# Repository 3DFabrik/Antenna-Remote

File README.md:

# Antenna Remote

Ein Antennenumschalter für bis zu acht Antennen auf einem ESP32. Er wählt die Antenne nach der Frequenz des Transceivers (Automatik) oder von Hand, zeigt alles auf einem Touch-Display und lässt sich über WLAN, Bluetooth und eine Weboberfläche bedienen. [SDROxide](https://github.com/3DFabrik/sdroxide) kann ihm die Frequenz direkt über WLAN schicken. Die Firmware ist eine Weiterentwicklung der Antenna Remote II.

Gedacht ist die Einheit für die Fernumschalter von [Amplitec](https://www.amplitec.hu/r_sw_3000_4_way_eng.html) (SW:3000) mit vier, sechs oder acht Wegen. Sie schaltet positiv und passt damit zu Umschaltern mit gemeinsamer Masse. Die Anzahl der Antennen (bis zu acht) wird in den Einstellungen gewählt.

Die Firmware-Version steht oben in der Weboberfläche. Ein Release-Build trägt den Tag als Version, ein lokaler Build seine Bauzeit.

## Was dazugehört

- **ESP32** Dev Module, 4 MB Flash. Die Partition `min_spiffs` hält zwei Programme vor, damit ein Update über WLAN möglich ist.
- **Touch-Display** ST7789, 320 × 240, quer eingebaut, mit Touch-Controller.
- **Schieberegister** 74HC164 für die Relais der acht Antennen. Genau ein Ausgang ist aktiv.
- **ICOM-Anschluss** (optional): CI-V an `Serial2` (19200 Baud, GPIO 16 und 17). Der Umschalter liest damit die Frequenz eines Icom. Andere Funkgeräte meldet ein `rigctld` im WLAN, siehe *Frequenzquelle*.

| Funktion | GPIO |
| --- | --- |
| Display MOSI, SCLK, MISO | 4, 18, 19 |
| Display CS, DC, RST | 15, 2, 23 |
| Touch CS | 21 |
| Schieberegister CLR, A/B, CLK | 25, 26, 27 |
| Relais externer Tuner, Relais Tune-Anforderung | 33, 32 |

Die Display-Pins stehen in `libraries/TFT_eSPI/User_Setup.h`. Beim ersten Start fragt das Display nach der Touch-Kalibrierung.

## Bedienung am Gerät

- **Seite 1** zeigt Frequenz, Band und die Antennenliste. `AUTOMATIC MODE` schaltet zwischen Automatik und Handbetrieb um. Zwischen diesem Schalter und `MISC` stehen zwei Symbole für die Verbindung: im Bluetooth-Modus das Bluetooth-Zeichen (grün, solange ein Client verbunden ist), im WLAN-Modus die Signalstärke (drei Bögen) und ein Bildschirm-Symbol, das grün wird, solange SDROxide verbunden ist. Die Weboberfläche zeigt dasselbe oben rechts. Im Handbetrieb wählen UP und DN die Antenne. Hält man `ST` eine Sekunde, wird die aktuelle Antenne für das aktuelle Band gespeichert. Im Automatikmodus heißt dieselbe Taste `TU` und startet den Tuner, siehe unten.
- **Seite 2** (`MISC`) zeigt die Verbindung: Modus, SSID, Status, IP, Signal, ob SDROxide verbunden ist, Antenne und Automatik. Hier wird auch der Verbindungsmodus eingestellt.

## Tuner

In den Einstellungen der Weboberfläche lässt sich pro Antenne das Häkchen `External Tuner` setzen. Ist es für die gewählte Antenne gesetzt, schaltet der Umschalter das erste Relais (GPIO 33) für den externen Tuner. Damit ist der Antennentuner des Transceivers abgeschaltet.

Die Taste `TU` (Display, Automatikmodus) und `TUNING` (Weboberfläche) sind nur dann aktiv, wenn die gewählte Antenne diese Markierung hat. Sonst sind sie grau. Ein Druck löst über das zweite Relais (GPIO 32) für genau fünf Sekunden die Tune-Anforderung aus, auch wenn der Finger auf der Taste bleibt. Der Transceiver sendet dann ein Signal mit geringer Leistung, auf das sich der externe Tuner abstimmt. Während der Anforderung ist die Taste rot. Ein erneuter Druck bricht sie ab, ebenso ein Wechsel der Antenne oder des Modus.

## Frequenzquelle und Bänder

In den Einstellungen der Weboberfläche wählt man unter *Frequency source*, woher der Umschalter die Frequenz liest:

- **None:** Er liest keine Frequenz. Sie kann trotzdem vom Windows-Programm mit `<QRG,…>` (USB oder Bluetooth) kommen.
- **Icom CI-V:** Er liest die Frequenz eines Icom über `Serial2`. Der TRX-Typ wird dazu gewählt. Einmal pro Sekunde fragt er auch den Sendezustand ab (CI-V-Befehl `1C 00`). Antwortet das Funkgerät darauf nicht, gibt es keine RX/TX-Anzeige.
- **Hamlib rigctld:** Im WLAN-Modus verbindet er sich mit einem `rigctld` (Hamlib), flrig oder dem Hamlib-Server von SDROxide und fragt zweimal pro Sekunde die Frequenz (`f`) und den Sendezustand (`t`) ab. Host (am besten als IP-Adresse) und Port (Vorgabe 4532) werden eingetragen. Ein Beispiel für Hamlib: `rigctld -m <Modell> -r COM3 -s 19200 -T 0.0.0.0`, die Modellnummer zeigt `rigctld -l`. `rigctld` hat keine Anmeldung und muss im LAN erreichbar sein, deshalb nur im Heimnetz einsetzen. Der Umschalter schickt nur Lesebefehle.
- **SDROxide:** SDROxide verbindet sich mit dem Umschalter (Port 4540) und schickt die Frequenz, siehe unten. Die Frequenz von SDROxide wird nur bei dieser Auswahl übernommen. Die übrigen Befehle (Antenne wählen, Automatik) funktionieren bei jeder Quelle. Den Sendezustand meldet SDROxide mit dem Befehl `P`, siehe Tabelle unten.

Oben rechts in der Weboberfläche steht neben der WLAN-Stärke die gewählte Quelle (`CI-V`, `Hamlib` oder `SDROxide`). Der Punkt davor leuchtet grün, solange die Verbindung steht. Das Display zeigt neben dem Band `RX` (grün) oder `TX` (rot), sobald die Quelle den Sendezustand liefert. Die Weboberfläche zeigt dasselbe oben links in der LCD-Anzeige. Beim Senden kommt dort das SWR dazu: bei `rigctld` per `l SWR`, sofern das Funkgerät es meldet (SDROxides eigener Hamlib-Server tut das nicht), bei Icom CI-V per `15 12` (nach der SWR-Skala des Icom, über 3 nur grob) und bei SDROxide mit dem Befehl `W`.

Auf Seite 2 steht die Quelle in der Zeile `SOURCE`. Auch über die serielle Konsole lässt sie sich setzen: `<freq_src,0>` (keine), `<freq_src,1>` (CI-V), `<freq_src,2>` (rigctld) oder `<freq_src,3>` (SDROxide), dazu `<rig_host,192.168.1.20>` und `<rig_port,4532>`.

**Sendeschutz:** Meldet die Quelle, dass das Funkgerät sendet, schaltet der Umschalter keine Antenne um. Der Wechsel (Automatik, Handbetrieb oder Weboberfläche) wird erst am Ende des Sendens ausgeführt, bis dahin steht `waiting for RX` auf der Webseite. Bricht die Meldung ab, gilt das als Empfang. Der Sendezustand kommt bei `rigctld` vom Befehl `t`, bei CI-V von `1C 00` und bei SDROxide vom Befehl `P`. Meldet eine Quelle ihn nicht, steht das in den Einstellungen und es gibt weder RX/TX-Anzeige noch Schutz.

**Bandgrenzen:** In den Einstellungen unter *Band limits* stehen Unter- und Obergrenze jedes Bandes in kHz. Die Vorgabe ist Region 1. Mit der Auswahl gibt es Voreinstellungen für Region 2 und 3, jeder Wert lässt sich verändern. Steht bei einem Band 0 und 0, ist es abgeschaltet. Liegt die Frequenz in keinem Band, bleibt die Antenne wie sie ist.

## Verbindung: Bluetooth oder WLAN

Der Umschalter läuft entweder mit Bluetooth oder mit WLAN, nie mit beidem. Auf Seite 2 wechselt `BT -> WLAN` (bzw. `WLAN -> BT`) den Modus. Das Gerät startet danach neu, und der Wechsel muss einmal bestätigt werden.

**WLAN einrichten:** Im WLAN-Modus öffnet `WLAN setup` eine Netzliste mit Scan. Das Netz antippen und das Passwort mit der Bildschirmtastatur eingeben (`Show` zeigt es im Klartext). Versteckte Netze gibt es über `HIDDEN`. Der Status auf Seite 2 nennt Fehler im Klartext, zum Beispiel `SSID not found` oder `Wrong password?`. Das Passwort liegt getrennt von der Konfiguration im Flash und wird nie ausgegeben.

Über die serielle Konsole (115200 Baud) geht es auch:

| Befehl | Wirkung |
| --- | --- |
| `<WIFI,ssid,passwort>` | speichert das WLAN (das Passwort darf Kommas enthalten) |
| `<NETMODE,wifi>` oder `<NETMODE,bt>` | Modus wählen, danach Neustart |
| `<WIFISTATUS>` | Modus, SSID, Status, IP und Signal |

## Weboberfläche

Im WLAN-Modus ist der Umschalter unter `http://<IP-Adresse>/` erreichbar. Die Seite passt sich der Fenstergröße an.

- **Main:** Frequenz in einer LCD-Anzeige, eine Taste pro Antenne, `AUTOMATIC`, `INT TUNER` und `TUNING`.
- **Settings:** Antennenanzahl, Namen, externer Tuner pro Antenne, Zuordnung der Bänder 160 bis 4 m, Bandgrenzen und Frequenzquelle. `Reboot` startet neu. `Reset` stellt die Werkseinstellungen her, behält aber den WLAN-Modus.
- **Update:** Firmware über den Browser einspielen, siehe unten.

Es gibt kein Passwort, der Umschalter gehört ins Heimnetz. Änderungen nimmt er nur per POST mit einem eigenen Header an, damit eine fremde Webseite ihn nicht schalten kann.

## SDROxide

In SDROxide unter Settings → Radio den Haken `Use Antenna Remote` setzen und unter Settings → Servers die IP-Adresse des Umschalters eintragen. Im Umschalter unter *Frequency source* `SDROxide` wählen. SDROxide zeigt dort, ob die Verbindung steht, und schickt die Frequenz des Radios. Die Automatik des Umschalters wählt danach die Antenne.

Das Protokoll ist Text über TCP, Port 4540, eine Zeile pro Befehl. Es kommt immer nur ein Client zum Zug. Ein weiterer wird abgewiesen, solange der erste mindestens einmal in zwei Sekunden fragt. Schweigt er länger, übernimmt ein neuer Client die Verbindung, nach fünf Sekunden Stille wird er getrennt.

| Anfrage | Antwort |
| --- | --- |
| `v` | `AntennaRemote 1` und `RPRT 0` |
| `F <Hz>` | `RPRT 0` (Frequenz des Radios in Hertz) |
| `s` | `ant=<1-8> auto=<0\|1> band=<m> n=<Anzahl> name=<Text>` und `RPRT 0` |
| `M <0\|1>` | `RPRT 0` (Automatik aus oder ein, ab Version 1.1.0) |
| `P <0\|1>` | `RPRT 0` (das Funkgerät empfängt oder sendet, ab Version 1.4.0; sollte bei jeder Änderung und mindestens alle 5 Sekunden kommen) |
| `W <SWR>` | `RPRT 0` (das SWR beim Senden, zum Beispiel `W 1.5`, ab Version 1.4.0; etwa zweimal pro Sekunde, solange gesendet wird) |
| `A <n>` | `RPRT 0` (Antenne `n` wählen und auf Handbetrieb schalten, ab Version 1.2.0) |

Alles andere beantwortet der Umschalter mit `RPRT -1`. SDROxide zeigt die aktive Antenne, einen Schalter für die Automatik und im Handbetrieb Tasten zum Weiterschalten in der Kopfleiste (Box `ANT SW`).

## Windows-Programm

Das Windows-Programm Antenna Remote V2 läuft weiter über Bluetooth oder die serielle Schnittstelle, auch mit OmniRig. Die Befehle in der Form `<ANTNUMBER,3,0>` sind unverändert. Antennen und Bandzuordnung lassen sich jetzt aber auch in der Weboberfläche pflegen.

## Firmware einspielen

Die Release-Dateien stehen unter *Releases*:

- `Antenna-Remote_ota.bin` ist das Programm für das **Update im Browser** (Reiter *Update*) oder per `curl`:
  `curl -H "X-AR: 1" -F "firmware=@Antenna-Remote_ota.bin" http://<IP>/update`
  Das Update läuft nur im WLAN-Modus. Vorher sollte nicht gesendet werden, denn der Umschalter startet danach neu.
  Die Weboberfläche prüft über den Browser (höchstens einmal am Tag) auf GitHub, ob es eine neuere Version gibt, und zeigt dann oben einen Hinweis mit Link zum Reiter *Update*. Dort führt ein Link zu den Dateien des Releases.
- `Antenna-Remote.bin` ist das Abbild für **USB**. Es wird ab Adresse 0 geschrieben:
  `esptool.py --chip esp32 write_flash 0x0 Antenna-Remote.bin`

## Selbst bauen

Arduino IDE oder `arduino-cli` mit dem Board-Paket `esp32:esp32` in Version **2.0.17**. Die mitgelieferte TFT_eSPI passt zu dieser Version, die Core-Reihe 3 baut sie nicht.

```
arduino-cli compile --fqbn esp32:esp32:esp32:PartitionScheme=min_spiffs --libraries libraries .
```

Die Bibliothek `libraries/TFT_eSPI` enthält die Pinbelegung des Displays. Beim Bauen in der Arduino IDE den Ordner `libraries` als Sketchbook-Bibliothek eintragen oder die Bibliothek dorthin kopieren.

## Release über GitHub

Ein Tag `v…` baut die Firmware auf GitHub und legt ein Release mit beiden Dateien an:

```
git tag v1.0.0
git push origin v1.0.0
```

Alternativ startet man *Actions → Release → Run workflow* und gibt die Version ein. Der Ablauf steht in `.github/workflows/release.yml`.

## Hardware

Die Platine liegt unter `hardware/` (KiCad):

- `kicad/` Projekt (Schaltplan, Leiterplatte), Stückliste und Netzliste
- `production/` Gerber- und Bohrdateien, `BOM.xlsx`
- `docs/` Schaltplan als PDF, Anschlussplan des Amplitec-Kabels
- `parts/` ESP32-DevKitC (Symbol, Footprint, 3D-Modell)
- `3d/` STEP-Modell der Platine

**Anschluss des Antennenumschalters (J1, DB9-Buchse):** Die Platine schaltet positiv. Die Relais des Amplitec-Umschalters hängen mit ihrem gemeinsamen Minus an Masse (Pin 3). Die Belegung folgt dem Plan von Amplitec (`hardware/docs/RSW(4)(6)8A1R_DSUB9_Connectors.pdf`). Antenne *n* schaltet das Relais `RLYn`:

| DB9-Pin | 1 | 2 | 3 | 4 | 5 | 6 | 7 | 8 | 9 |
| --- | --- | --- | --- | --- | --- | --- | --- | --- | --- |
| Signal | RLY8 | RLY7 | GND | RLY6 | RLY5 | RLY4 | RLY3 | RLY2 | RLY1 |

Beim 8-fach-Umschalter sind alle Pins belegt. Der 6-fach braucht Pin 3 und 4 bis 9, der 4-fach Pin 3 und 6 bis 9. Das Kabel hat an beiden Enden einen 9-poligen Stecker (male), der Schirm liegt am Metallgehäuse. Amplitec empfiehlt 0,25 mm² bis 70 m und 0,5 mm² bis 100 m Länge sowie einen Test des fertigen Kabels.

**Bekannte Fehler:**

- Der Buzzer (BZ1) ist im Schaltplan nicht richtig angeschlossen. Er hängt an GPIO 34, und der kann nur Eingang. Der Pin muss getauscht werden. Die Firmware steuert noch keinen Buzzer an.
- Der Buzzer sitzt auf der Leiterplatte zu nah am Rand und muss etwas weiter nach innen.

## Lizenz

MIT, siehe `LICENSE`. Die Bibliothek TFT_eSPI unter `libraries/TFT_eSPI` hat ihre eigene Lizenz (`license.txt`).

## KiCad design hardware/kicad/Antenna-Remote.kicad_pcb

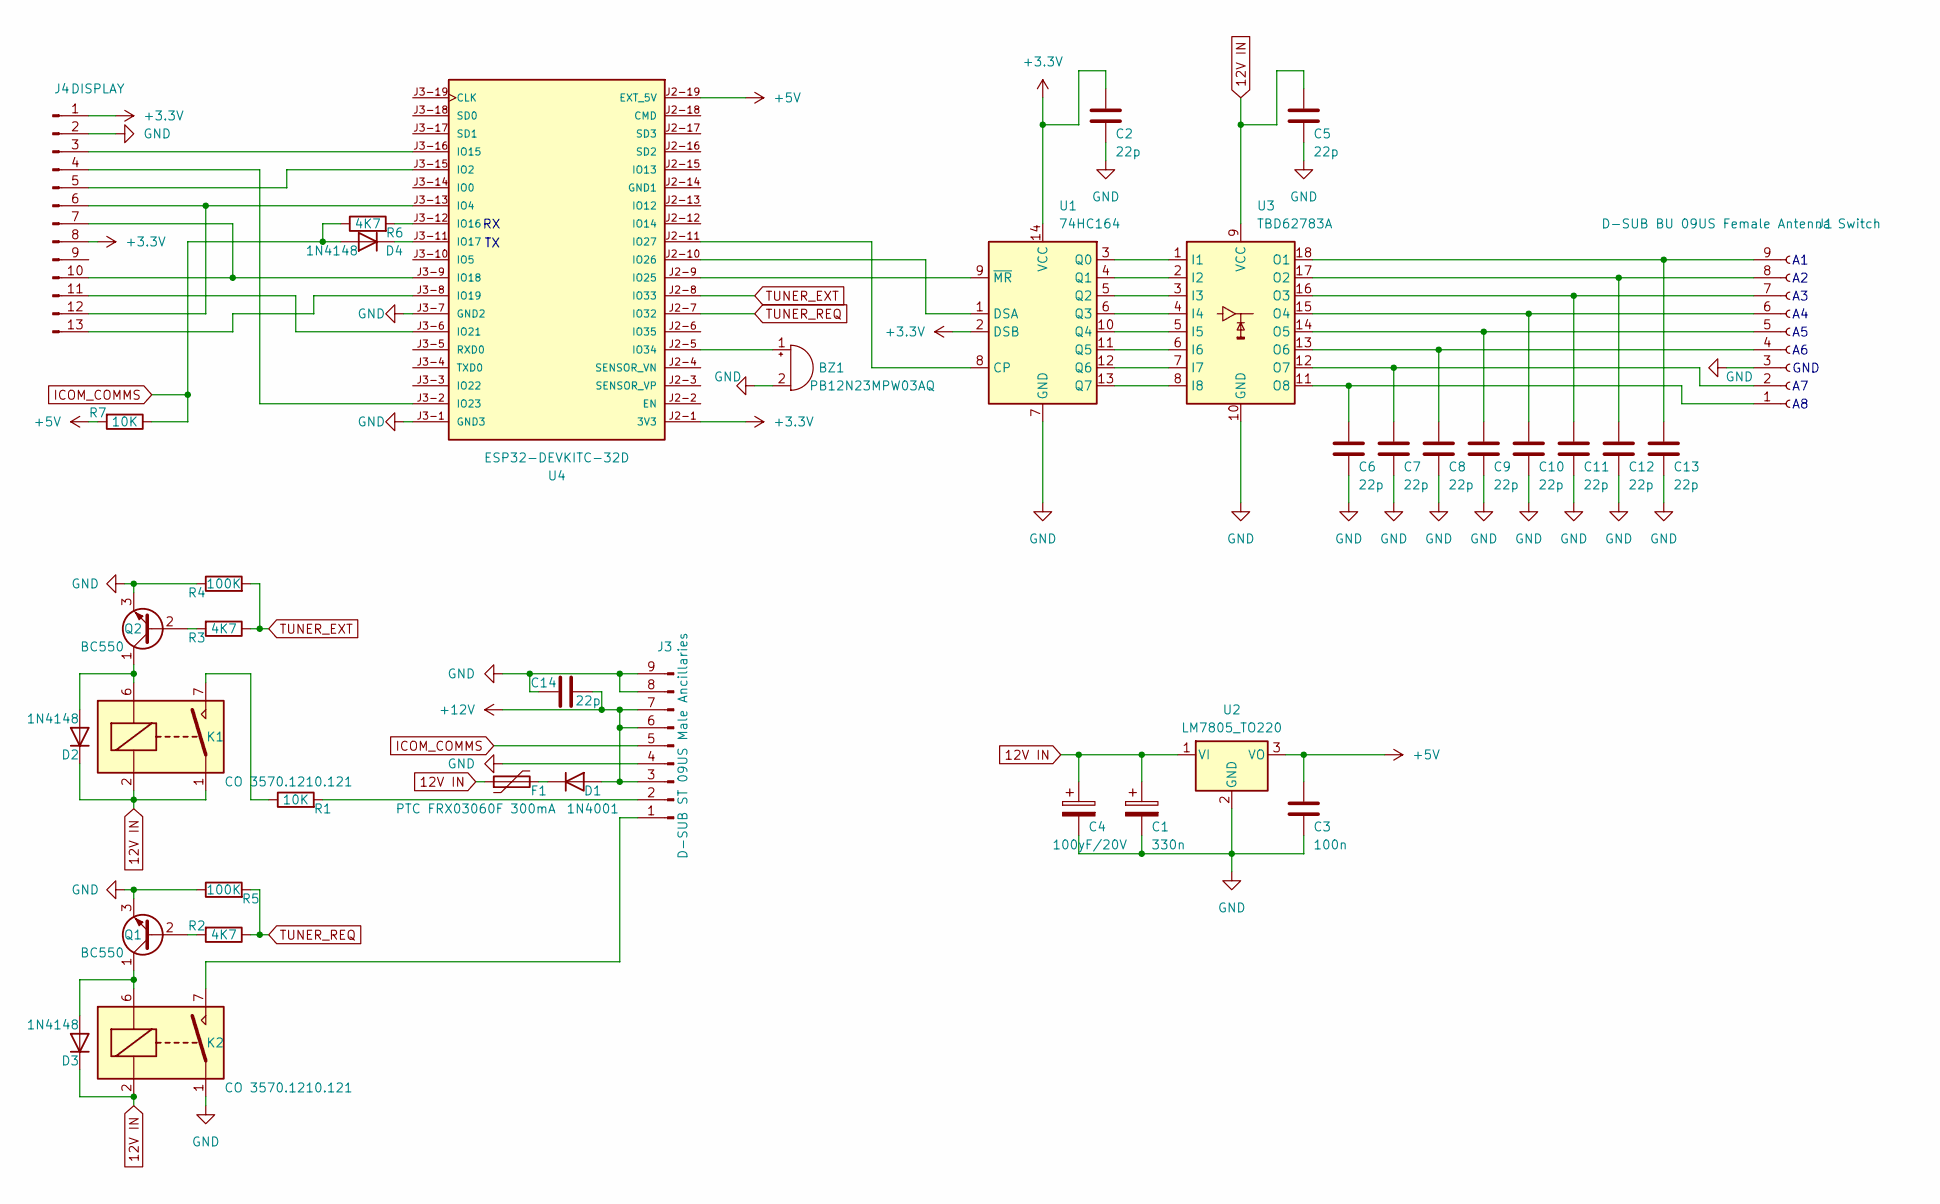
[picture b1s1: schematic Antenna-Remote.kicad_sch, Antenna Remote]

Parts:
BZ1: PB12N23MPW03AQ; Buzzer_12x9.5RM7.6
C1: 330n; C_Rect_L4.6mm_W2.0mm_P2.50mm_MKS02_FKP02
C2, C5, C6, C7, C8, C9, C10, C11, C12, C13, C14: 22p; C_Disc_D5.0mm_W2.5mm_P2.50mm
C3: 100n; C_Rect_L4.6mm_W2.0mm_P2.50mm_MKS02_FKP02
C4: 100yF/20V; CP_Radial_D5.0mm_P2.50mm
D1: 1N4001; D_DO-41_SOD81_P3.81mm_Vertical_KathodeUp
D2, D3, D4: 1N4148; D_DO-35_SOD27_P7.62mm_Horizontal
F1: PTC FRX03060F 300mA; Fuse_BelFuse_0ZRE0005FF_L8.3mm_W3.8mm
J1: D-SUB BU 09US Female Antenna Switch; DSUB-9_Female_Horizontal_P2.77x2.84mm_EdgePinOffset7.70mm_H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
J3: D-SUB ST 09US Male Ancillaries; DSUB-9_Male_Horizontal_P2.77x2.84mm_EdgePinOffset7.70mm_Hou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
J4: DISPLAY; PinHeader_1x13_P2.54mm_Vertical
K1, K2: CO 3570.1210.121; COMUS Reed-Relais 12 V DC, 10 W - 1 NO
Q1, Q2: BC550; TO-92L_Inline_Wide
R1, R7: 10K; R_Axial_DIN0207_L6.3mm_D2.5mm_P10.16mm_Horizontal
R2, R3, R6: 4K7; R_Axial_DIN0207_L6.3mm_D2.5mm_P10.16mm_Horizontal
R4, R5: 100K; R_Axial_DIN0207_L6.3mm_D2.5mm_P10.16mm_Horizontal
U1: 74HC164; DIP-14_W7.62mm_Socket
U2: LM7805_TO220; TO-220-3_Vertical
U3: TBD62783A; DIP-18_W7.62mm_Socket
U4: ESP32-DEVKITC-32D; MODULE_ESP32-DEVKITC-32D; PARTREV V4

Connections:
12V IN: C1.1, C4.1, C5.1, D2.1 (K), D3.1 (K), F1.1, K1.1, K1.2, K1.14, K2.2, U2.1 (VI), U3.9 (VCC)
+3.3V: C2.1, J4.1 (VCC), J4.8 (LED), U1.2 (DSB), U1.14 (VCC), U4.J2-1 (3V3)
+5V: C3.1, R7.2, U2.3 (VO), U4.J2-19 (EXT_5V)
+12V: C14.1, D1.2 (A), J3.3, J3.6, J3.7
GND: BZ1.2 (+), C1.2, C2.2, C3.2, C4.2, C5.2, C6.2, C7.2, C8.2, C9.2, C10.2, C11.2, C12.2, C13.2, C14.2, J1.3, J3.4, J3.8, J3.9, J4.2 (GND), K2.1, K2.14, Q1.3 (E), Q2.3 (E), R4.1, R5.1, U1.7 (GND), U2.2 (GND), U3.10 (GND), U4.J3-1 (GND3), U4.J3-7 (GND2)
ICOM_COMMS: D4.2 (A), J3.5, R6.1, R7.1
unnamed: BZ1.1 (-), U4.J2-5 (IO34)
unnamed: D1.1 (K), F1.2
unnamed: D2.2 (A), K1.6, Q2.1 (C)
unnamed: D3.2 (A), K2.6, Q1.1 (C)
unnamed: D4.1 (K), U4.J3-11 (IO17)
unnamed: C6.1, J1.1, U3.11 (O8)
unnamed: C7.1, J1.2, U3.12 (O7)
unnamed: C8.1, J1.4, U3.13 (O6)
unnamed: C9.1, J1.5, U3.14 (O5)
unnamed: C10.1, J1.6, U3.15 (O4)
unnamed: C11.1, J1.7, U3.16 (O3)
unnamed: C12.1, J1.8, U3.17 (O2)
unnamed: C13.1, J1.9, U3.18 (O1)
unnamed: J3.1, K2.7, K2.8
unnamed: J3.2, R1.2
unnamed: J4.3, U4.J3-16 (IO15)
unnamed: J4.4, U4.J3-2 (IO23)
unnamed: J4.5, U4.J3-15 (IO2)
unnamed: J4.7, J4.10, U4.J3-9 (IO18)
unnamed: J4.11, U4.J3-6 (IO21)
unnamed: J4.6, J4.12, U4.J3-13 (IO4)
unnamed: J4.13, U4.J3-8 (IO19)
unnamed: K1.7, K1.8, R1.1
unnamed: Q1.2 (B), R2.2
unnamed: Q2.2 (B), R3.2
unnamed: U1.8 (CP), U4.J2-11 (IO27)
unnamed: U1.1 (DSA), U4.J2-10 (IO26)
unnamed: U1.3 (Q0), U3.1 (I1)
unnamed: U1.4 (Q1), U3.2 (I2)
unnamed: U1.5 (Q2), U3.3 (I3)
unnamed: U1.6 (Q3), U3.4 (I4)
unnamed: U1.10 (Q4), U3.5 (I5)
unnamed: U1.11 (Q5), U3.6 (I6)
unnamed: U1.12 (Q6), U3.7 (I7)
unnamed: U1.13 (Q7), U3.8 (I8)
unnamed: U1.9 (~MR), U4.J2-9 (IO25)
unnamed: R6.2, U4.J3-12 (IO16)
TUNER_EXT: R3.1, R4.2, U4.J2-8 (IO33)
TUNER_REQ: R2.1, R5.2, U4.J2-7 (IO32)

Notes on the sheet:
GND

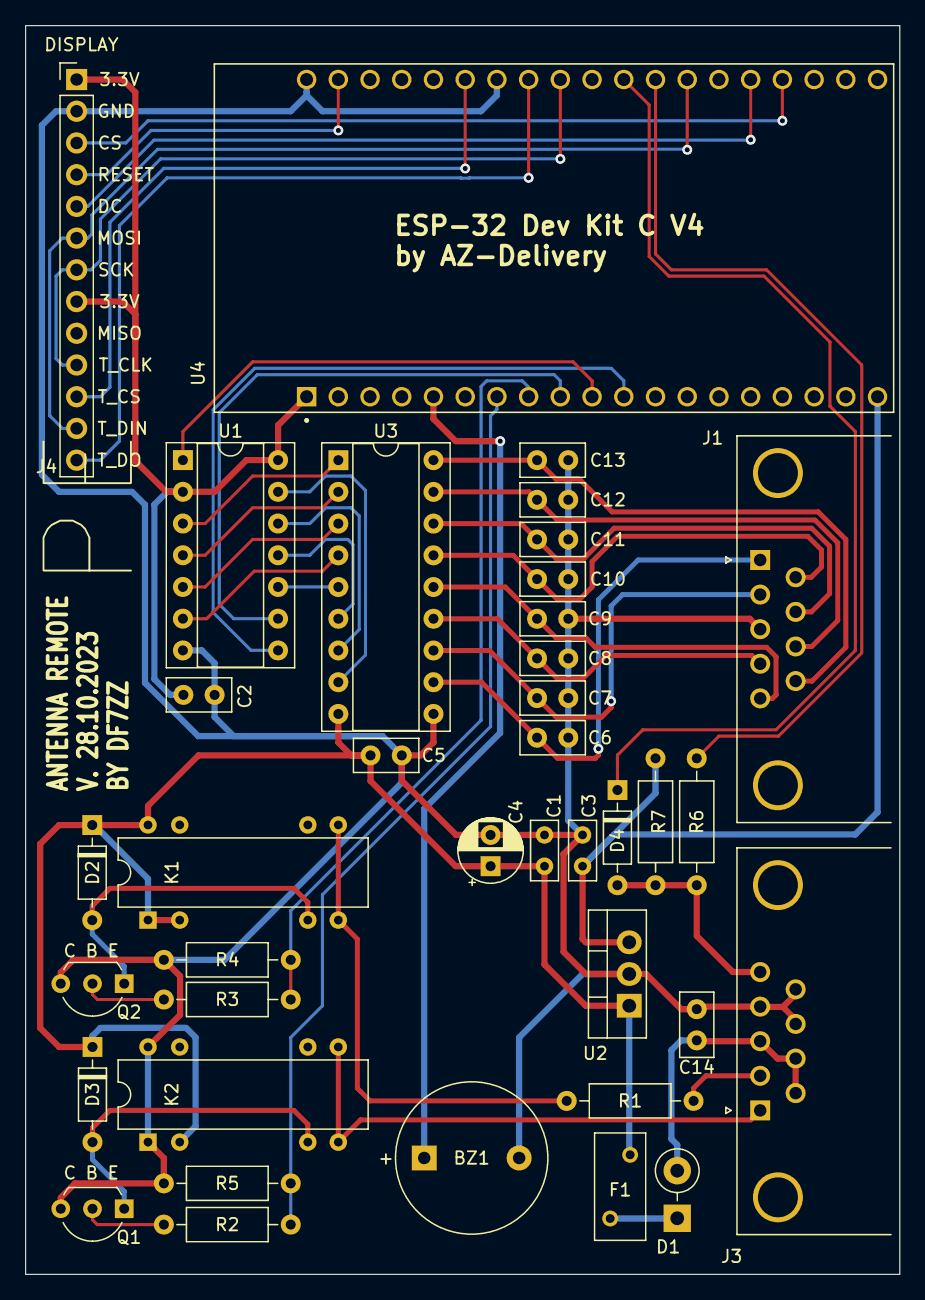
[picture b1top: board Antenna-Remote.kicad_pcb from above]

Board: 2 copper layers, 70.0 x 100.0 mm, 38 parts (0 on the bottom side), 45 nets.

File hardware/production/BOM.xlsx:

Source: | U:\Hobby\Funkerei\Antennenumschalter\PCB\Antennenumschalter_ESP32 - V3\Antennen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
Date: | 45241.597013888888
Tool: | Eeschema 7.0.7
Generator: | C:\Program Files\KiCad\7.0\bin\scripting\plugins/bom_csv_grouped_by_value.py
Component Count: | 38
Collated Components:
Item | Qty | Reference(s) | Value | LibPart | Footprint | Datasheet | DNP | Availability | Check_prices | Description | MANUFACTURER | MAXIMUM_PACKAGE_HEIGHT | MF | MP | PARTREV | Package | Price | Purchase-URL | SNAPEDA_PN | STANDARD | Sim.Device | Sim.Pins | SnapEDA_Link
1 | 1 | BZ1 | PB12N23MPW03AQ | Device:Buzzer | Buzzer_Beeper:Buzzer_12x9.5RM7.6 | https://www.reichelt.de/index.html?ACTION=7&LA=3&OPEN=0&INDE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
2 | 1 | C1 | 330n | Device:C_Polarized | Capacitor_THT:C_Rect_L4.6mm_W2.0mm_P2.50mm_MKS02_FKP02 | ~
3 | 11 | C2, C5, C6, C7, C8, C9, C10, C11, C12, C13, C14 | 22p | Device:C | Capacitor_THT:C_Disc_D5.0mm_W2.5mm_P2.50mm | ~
4 | 1 | C3 | 100n | Device:C | Capacitor_THT:C_Rect_L4.6mm_W2.0mm_P2.50mm_MKS02_FKP02 | ~
5 | 1 | C4 | 100yF/20V | Device:C_Polarized | Capacitor_THT:CP_Radial_D5.0mm_P2.50mm | ~
6 | 1 | D1 | 1N4001 | Device:D | Diode_THT:D_DO-41_SOD81_P3.81mm_Vertical_KathodeUp | ~ |  |  |  |  |  |  |  |  |  |  |  |  |  |  | D | 1=K 2=A
7 | 3 | D2, D3, D4 | 1N4148 | Diode:BA243 | Diode_THT:D_DO-35_SOD27_P7.62mm_Horizontal | https://www.reichelt.de/schalt-diode-100-v-150-ma-do-35-1n-4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 |  |  |  |  |  |  |  |  |  |  |  |  |  |  | D | 1=K 2=A
8 | 1 | F1 | PTC FRX03060F 300mA | Device:Polyfuse | Fuse:Fuse_BelFuse_0ZRE0005FF_L8.3mm_W3.8mm | https://www.reichelt.de/index.html?ACTION=7&LA=3&OPEN=0&INDE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
9 | 1 | J1 | D-SUB BU 09US Female Antenna Switch | Connector:Conn_01x09_Socket | Connector_Dsub:DSUB-9_Female_Horizontal_P2.77x2.84mm_EdgePinOffset7.70mm_Housed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 | https://www.reichelt.de/index.html?ACTION=446&LA=446&nbc=1&q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
10 | 1 | J3 | D-SUB ST 09US Male Ancillaries | Connector:Conn_01x09_Pin | Connector_Dsub:DSUB-9_Male_Horizontal_P2.77x2.84mm_EdgePinOffset7.70mm_Housed_M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 | https://www.reichelt.de/index.html?ACTION=446&LA=446&nbc=1&q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
11 | 1 | J4 | DISPLAY | Connector:Conn_01x13_Pin | Connector_PinHeader_2.54mm:PinHeader_1x13_P2.54mm_Vertical | ~
12 | 2 | K1, K2 | CO 3570.1210.121 | Relay:DIPxx-1Axx-11x | Relay_THT:COMUS Reed-Relais 12 V DC, 10 W - 1 NO | https://www.reichelt.de/reed-relais-12-v-dc-10-w-1-no-co-357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
13 | 2 | Q1, Q2 | BC550 | Transistor_BJT:BC550 | Package_TO_SOT_THT:TO-92L_Inline_Wide | https://www.onsemi.com/pub/Collateral/BC550-D.pdf
14 | 2 | R1, R7 | 10K | Device:R | Resistor_THT:R_Axial_DIN0207_L6.3mm_D2.5mm_P10.16mm_Horizontal | ~
15 | 3 | R2, R3, R6 | 4K7 | Device:R | Resistor_THT:R_Axial_DIN0207_L6.3mm_D2.5mm_P10.16mm_Horizontal | ~
16 | 2 | R4, R5 | 100K | Device:R | Resistor_THT:R_Axial_DIN0207_L6.3mm_D2.5mm_P10.16mm_Horizontal | ~
17 | 1 | U1 | 74HC164 | 74xx:74HC164 | Package_DIP:DIP-14_W7.62mm_Socket | https://www.reichelt.de/schieberegister-8-bit-seriell-zu-par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
18 | 1 | U2 | LM7805_TO220 | Regulator_Linear:LM7805_TO220 | Package_TO_SOT_THT:TO-220-3_Vertical | https://www.onsemi.cn/PowerSolutions/document/MC7800-D.PDF
19 | 1 | U3 | TBD62783A | Transistor_Array:TBD62783A | Package_DIP:DIP-18_W7.62mm_Socket | http://toshiba.semicon-storage.com/info/docget.jsp?did=30523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
20 | 1 | U4 | ESP32-DEVKITC-32D | ESP32-DEVKITC-32D:ESP32-DEVKITC-32D | esp32_DevKitC:MODULE_ESP32-DEVKITC-32D |  |  | In Stock | https://www.snapeda.com/parts/ESP32-DEVKITC-32D/Espressif+Sy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 | WiFi Development Tools (802.11) ESP32 General Development Kit, ESP32-WROOM-32D 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 | Espressif Systems | N/A | Espressif Systems | ESP32-DEVKITC-32D | V4 | None | None | https://www.snapeda.com/api/url_track_click_mouser/?unipart_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 | ESP32-DEVKITC-32D | Manufacturer Recommendations |  |  | https://www.snapeda.com/parts/ESP32-DEVKITC-32D/Espressif+Sy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
